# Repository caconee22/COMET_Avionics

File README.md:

# COMET_Avionics

COMET rocket avionics hardware project archive.

This repository replaces the previous `COMET_ROK_2` repository with the full
COMET avionics workspace layout.

## Structure

- `ROK2025/`: ROK2-era module board and reference files.
- `ROK2026/`: Current ROK2026 KiCad projects, shared libraries, and revisions.
- `ROK2026/ROK_3/`: ROK3 small-form-factor and SMD-chip test board.
- `ROK2026/ROK_4/`: ROK4 power-design research test board.
- `ROK2026/Away_1/`: Current active avionics candidate version under development.

## Project History

- `ROK2025/COMET_ROK_2`: First ROK2 circuit and module board. It was not used
  because of software development staffing issues.
- `ROK2026/ROK_3`: Miniaturized ROK3 version with SMD chips. It was not used
  because of power-section issues, but it may still be recoverable and remains
  a test version.
- `ROK2026/ROK_4`: A further test version focused on power-section design. It
  is a research version for a small buck-converter power design.
- `ROK2026/Away_1`: The avionics version candidate intended for actual use. It
  is currently under development.

## Avionics Design Intent

This design intent applies to the whole COMET avionics board family.

## 설계 목적

COMET_Avionics의 목적은 단순한 데이터 로거가 아니라, 로켓 비행 중 필요한
항공전자 기능을 안정적으로 수행하는 것이다.

가장 중요한 기능은 최고점 판단, 지연 사출 판단, 그리고 실제 사출 작동이다.
로그 저장, 통신, GPS 전송, LED, 부저, 콘솔 출력은 모두 보조 기능이며,
이 기능들이 사출 판단과 작동을 막아서는 안 된다.

## 우선순위 규약

1. 사출 판단과 사출 작동을 최우선으로 둔다.
2. SD카드 기록, LoRa, MQTT, Wi-Fi/LTE, GPS 텔레메트리, LED, 부저, 콘솔은
   사출 경로를 블로킹하지 않아야 한다.
3. 센서 감시는 100Hz 이상을 기본 목표로 한다.
4. 저장과 통신은 큐나 별도 작업으로 분리해 지연이 생겨도 비행 판단에 영향을
   주지 않게 한다.
5. 실제 비행 적용 전에는 회로, 펌웨어, 전원부, 사출부를 별도로 검증해야 한다.

## 센서와 비행 판단

기본 설계 방향은 압력 센서, IMU, 배터리 전압, 사출 감지, GPS 최신값을 함께
다루는 것이다.

`Away_1`의 메인 IMU는 STMicroelectronics `LSM6DSO32XTR`를 채택한다.
이 센서는 3축 가속도, 3축 자이로, 온도 센서를 포함하며, 가속도는 최대
±32g, 자이로는 최대 ±2000dps 범위를 기준으로 사용할 수 있다.

비행 중에는 발사 감지, 최고점 판단, 지연 사출, 착지 판단, 회수 모드 진입을
이벤트로 남긴다. 고도, 필터링된 속도, 가속도 크기, 발사/최고점 판단 점수,
GPS 속도와 방향처럼 후처리가 가능한 값은 가능한 한 뷰어나 분석 도구에서
계산한다.

## 어포지 판단 예비 기준

어포지 판단은 센서 하나만으로 결정하지 않고, 기압 고도, IMU 상태, 시간 조건을
함께 보는 상태머신으로 구성한다. 초기 로켓은 발사 실패, 중간 고도 이후 뒤집힘,
상하 반전, 과격한 회전, 불안정 비행이 생길 수 있으므로 정상 비행만 가정하지
않는다.

기본 상태 흐름은 다음을 기준으로 한다.

1. `PAD`: 발사 전 대기 상태.
2. `LAUNCHED`: 발사 감지 후 상승 시작 상태.
3. `COAST_NORMAL`: 정상 상승/관성 비행으로 판단되는 상태.
4. `UNSTABLE_FLIGHT`: 뒤집힘, 과격한 회전, 고도 상승 이상 등 비정상 비행 상태.
5. `APOGEE_DETECTED`: 어포지 또는 하강 시작이 확인된 상태.
6. `FAILSAFE_DEPLOY`: 센서 이상이나 비정상 비행으로 백업 사출이 필요한 상태.
7. `RECOVERY`: 사출 이후 회수 상태.

정상 어포지 판단은 다음 조건을 함께 본다.

- 발사 감지가 완료되어 있을 것.
- 발사 후 최소 사출 금지 시간이 지났을 것.
- 필터링된 기압 고도 기준 최고 고도를 추적할 것.
- 현재 고도가 최고 고도보다 일정량 이상 낮아질 것.
- 필터링된 수직 속도가 음수 방향일 것.
- 위 조건이 짧은 시간 동안 지속될 것.

초기 기준값은 다음 범위에서 시험하며 조정한다.

- 최소 사출 금지 시간: 발사 후 1~2초.
- 고도 하락 판단: 최고 고도 대비 2~5m 하락.
- 하강 지속 시간: 200~500ms.
- 백업 사출 시간: 예상 어포지 이후를 기준으로 별도 시험값 설정.

비정상 비행 판단은 다음 상황을 감지하는 방향으로 둔다.

- 자이로 회전율이 일정 시간 이상 매우 큰 상태.
- 가속도 방향이 계속 급격하게 바뀌는 상태.
- 발사 후 고도 상승이 거의 없거나 예상보다 빨리 멈추는 상태.
- 고도 상승 후 불규칙한 정체와 하락이 반복되는 상태.
- IMU 축 기준 위아래 판단이 신뢰하기 어려운 상태.

비정상 비행 상태에서는 IMU 적분 고도나 자세 기준 판단에 의존하지 않는다.
기압 고도 변화, 시간 조건, 회전 이상 감지를 우선 사용하고, 필요하면 정상
어포지보다 보수적인 백업 사출 조건으로 전환한다.

개념적인 판단식은 다음과 같다.

```text
if launched and time_since_launch > min_deploy_time:
    if altitude_peak - altitude_filtered > altitude_drop_threshold
       and vertical_velocity_filtered < 0
       and falling_duration > falling_hold_time:
        apogee_detected = true

    if unstable_flight and altitude_not_increasing:
        failsafe_deploy = true

    if time_since_launch > max_flight_time:
        failsafe_deploy = true
```

이 기준은 비행 검증 완료값이 아니라 초기 개발용 예비 기준이다. 실제 임계값은
기체 질량, 모터 추력 곡선, 벤트홀 설계, 지상 시험, 저고도 시험 결과를 보고
조정한다.

## 로그 규약

로그는 텍스트보다 바이너리 형식을 우선한다.

- `LOG`: 고정 길이 센서 샘플
- `EVENT`: 발사, 최고점, 사출, 착지, 전압 변화, SD 오류, 파일 회전, 통신 상태,
  GPS fix/loss, 회수 모드 진입 같은 이벤트 기록

`LOG`에는 시간 코드, 시퀀스 번호, 상태 플래그, 압력, 온도, IMU 가속도/자이로,
최신 GPS 위도/경도/고도, GPS 플래그, 배터리 전압, 사출 센서 상태 같은
raw/minimal 값을 저장하는 방향으로 둔다.

## 로그 동작 흐름

패드 대기 또는 armed 상태에서는 최근 약 3초 분량의 100Hz RAM prebuffer를
유지한다. 평상시 저장은 10Hz 정도로 제한할 수 있다.

발사가 감지되면 발사 직전 prebuffer와 발사 이후 데이터를 100Hz로 저장한다.
최고점/사출 이후 하강 구간은 짧은 시간 단위 파일로 분리하는 방향을 둔다.

착지가 10초 이상 안정적으로 확인되면 고속 로그를 닫고, 회수/저전력 모드로
전환한다. 이 상태에서는 1Hz 수준으로 로그를 줄이고 GPS 위치를 LoRa와 MQTT로
전송하는 것을 목표로 한다.

## 통신과 회수

LoRa 433MHz는 지상국과 회수용 통신을 위한 기본 방향으로 둔다.
MQTT는 온보드 Wi-Fi/LTE 라우터를 통한 원격 모니터링 또는 회수 보조 용도로
사용할 수 있다.

통신 실패는 비행 판단 실패로 이어지면 안 된다. 통신은 가능한 경우 보내고,
안 되는 경우에는 로그와 사출 판단이 계속 살아 있어야 한다.

## 검증 기준

이 문서는 COMET_Avionics 전체 보드에 적용되는 설계 의도와 개발 규약이다.
각 보드는 실제 비행 적용 전 회로, 펌웨어, 전원부, 사출부를 별도로 검증해야
하며, README에 적힌 내용만으로 비행 검증 완료를 의미하지 않는다.

Temporary extraction/work folders such as `tmp/` and `tmp_pdf_kmg/` are not
tracked.

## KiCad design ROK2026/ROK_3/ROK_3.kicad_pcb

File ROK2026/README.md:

# ROK2026

COMET ROK 2026 hardware project workspace.

## Projects

- `ROK_3`: Miniaturized ROK3 SMD-chip test board.
- `ROK_4`: ROK4 power-section design and small buck-converter research board.
- `Away_1`: Active avionics candidate version under development.

## Board Status

- `ROK_3`: Small-form-factor version using SMD chips. It was not used because
  of power-section issues, but it may still be recoverable and remains a test
  version.
- `ROK_4`: Further test version for power-section design. It is a research
  board for the small buck-converter power design.
- `Away_1`: The candidate avionics version intended for actual use. This is the
  current development target.

## Away_1

`Away_1` is the active candidate for the real avionics version.
It is currently under development.

The avionics design intent and development rules apply to the whole board
family and are documented in the root `README.md`.

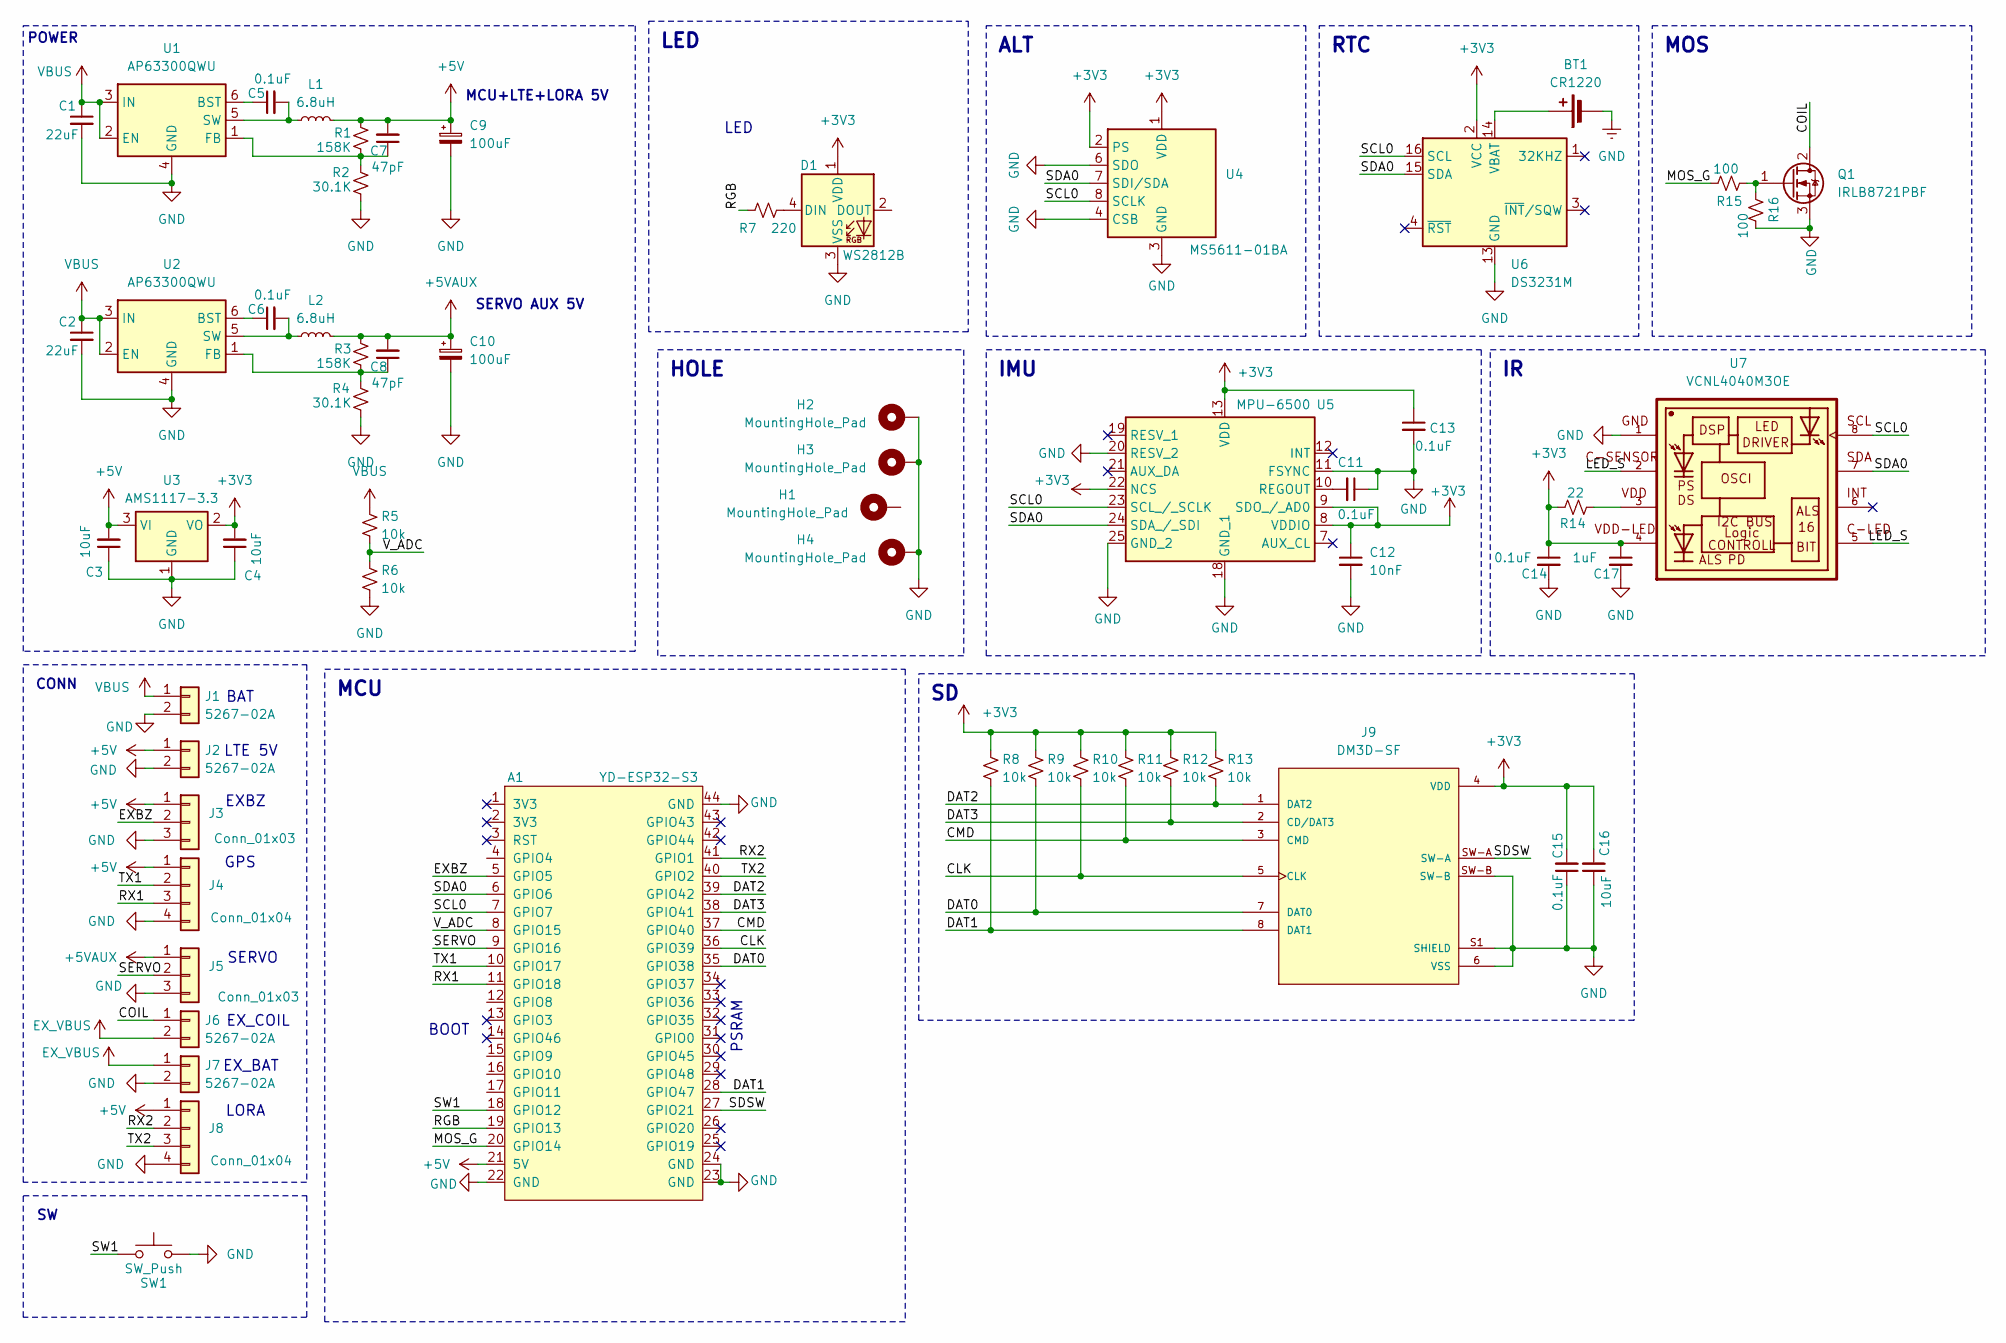
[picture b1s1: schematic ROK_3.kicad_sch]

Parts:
A1: YD-ESP32-S3
BT1: CR1220; S8411-45R_1; Manufacturer_Part_Number CR1220-2; LCSC C70381
C1, C2: 22uF; C_0805_2012Metric
C3, C4, C16: 10uF; C_0805_2012Metric
C5, C6, C14: 0.1uF; C_0805_2012Metric
C7, C8: 47pF; C_0805_2012Metric
C9, C10: 100uF; CP_Elec_6.3x5.3
C11, C13: 0.1uF; C_0805_2012Metric; LCSC C14663
C12: 10nF; C_0805_2012Metric; LCSC C57112
C15: 0.1uF; C_0805_2012Metric; Manufacturer_Part_Number CC0603KRX7R9BB104; LCSC C14663
C17: 1uF; C_0805_2012Metric
D1: WS2812B; LED_WS2812B_PLCC4_5.0x5.0mm_P3.2mm
H1, H2, H3, H4: MountingHole_Pad; MountingHole_3.2mm_M3_DIN965_Pad
J1, J7: 5267-02A; AMASS_XT30U-F_1x02_P5.0mm_Vertical
J2: 5267-02A; Molex_SPOX_5267-02A_1x02_P2.50mm_Vertical
J3, J5: Conn_01x03; Molex_SPOX_5267-03A_1x03_P2.50mm_Vertical
J4, J8: Conn_01x04; Molex_SPOX_5267-04A_1x04_P2.50mm_Vertical
J6: 5267-02A; TerminalBlock_4Ucon_1x02_P3.50mm_Horizontal
J9: DM3D-SF; HRS_DM3D-SF; PARTREV 2017.1
L1, L2: 6.8uH; L_Sumida_CDMC6D28_7.25x6.5mm
Q1: IRLB8721PBF; TO-220-3_Horizontal_TabDown
R1, R3: 158K; R_0805_2012Metric
R2, R4: 30.1K; R_0805_2012Metric
R5, R6, R8, R9, R10, R11, R12, R13: 10k; R_0805_2012Metric; LCSC C25804
R7: 220; R_0805_2012Metric_Pad1.20x1.40mm_HandSolder
R14: 22; R_0805_2012Metric; LCSC C25804
R15, R16: 100; R_0805_2012Metric; LCSC C25804
SW1: SW_Push; SW_PUSH_6mm_H5mm
U1, U2: AP63300QWU; TSOT-23-6
U3: AMS1117-3.3; SOT-223-3_TabPin2
U4: MS5611-01BA; LGA-8_3x5mm_P1.25mm
U5: MPU-6500; QFN-24-1EP_3x3mm_P0.4mm_EP1.75x1.6mm; Manufacturer_Part_Number MPU-6500; Mouser Part Number 410-MPU-6500
U6: DS3231M; SOIC-16W_7.5x10.3mm_P1.27mm
U7: VCNL4040M3OE; VISHAY_VCNL4040_4X2X1.1

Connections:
+3V3: C4.2, C12.1, C13.1, C14.1, C15.2, C16.2, C17.1, D1.1 (VDD), J9.4 (VDD), R8.2, R9.2, R10.2, R11.2, R12.2, R13.2, R14.2, U3.2 (VO), U4.1 (VDD), U4.2 (PS), U5.8 (VDDIO), U5.9 (SDO_/_AD0), U5.13 (VDD), U5.22 (NCS), U6.2 (VCC), U7.4
+5V: A1.21 (5V), C3.2, C7.2, C9.1, J2.1, J3.1, J4.1, J8.1, L1.2, R1.1, U3.3 (VI)
+5VAUX: C8.2, C10.1, J5.1, L2.2, R3.1
/CLK: A1.36 (GPIO39), J9.5 (CLK), R10.1
/CMD: A1.37 (GPIO40), J9.3 (CMD), R11.1
/COIL: J6.1, Q1.2 (D)
/DAT0: A1.35 (GPIO38), J9.7 (DAT0), R9.1
/DAT1: A1.28 (GPIO47), J9.8 (DAT1), R8.1
/DAT2: A1.39 (GPIO42), J9.1 (DAT2), R13.1
/DAT3: A1.38 (GPIO41), J9.2 (CD/DAT3), R12.1
/EXBZ: A1.5 (GPIO5), J3.2
/LED_S: U7.2, U7.5
/MOS_G: A1.20 (GPIO14), R15.2
/RGB: A1.19 (GPIO13), R7.2
/RX1: A1.11 (GPIO18), J4.3
/RX2: A1.41 (GPIO1), J8.2
/SCL0: A1.7 (GPIO7), U4.8 (SCLK), U5.23 (SCL_/_SCLK), U6.16 (SCL), U7.8
/SDA0: A1.6 (GPIO6), U4.7 (SDI/SDA), U5.24 (SDA_/_SDI), U6.15 (SDA), U7.7
/SDSW: A1.27 (GPIO21), J9.SW-A
/SERVO: A1.9 (GPIO16), J5.2
/SW1: A1.18 (GPIO12), SW1.1
/TX1: A1.10 (GPIO17), J4.2
/TX2: A1.40 (GPIO2), J8.3
/V_ADC: A1.8 (GPIO15), R5.1, R6.2
EX_VBUS: J6.2, J7.1
GND: A1.22 (GND), A1.23 (GND), A1.24 (GND), A1.44 (GND), BT1.2 (-), C1.2, C2.2, C3.1, C4.1, C9.2, C10.2, C11.1, C12.2, C13.2, C14.2, C15.1, C16.1, C17.2, D1.3 (VSS), H2.1 (1_1), H3.1 (1_1), H4.1 (1_1), J1.2, J2.2, J3.3, J4.4, J5.3, J7.2, J8.4, J9.6 (VSS), J9.S1 (SHIELD), J9.S2 (SHIELD), J9.S3 (SHIELD), J9.S4 (SHIELD), J9.SW-B, Q1.3 (S), R2.1, R4.1, R6.1, R16.2, SW1.2, U1.4 (GND), U2.4 (GND), U3.1 (GND), U4.3 (GND), U4.4 (CSB), U4.5 (CSB), U4.6 (SDO), U5.11 (FSYNC), U5.18 (GND_1), U5.20 (RESV_2), U5.25 (GND_2), U6.5 (GND), U6.6 (GND), U6.7 (GND), U6.8 (GND), U6.9 (GND), U6.10 (GND), U6.11 (GND), U6.12 (GND), U6.13 (GND), U7.1
unnamed: BT1.1 (+), U6.14 (VBAT)
unnamed: D1.4 (DIN), R7.1
unnamed: Q1.1 (G), R15.1, R16.1
unnamed: R14.1, U7.3
unnamed: C5.1, U1.6 (BST)
unnamed: C7.1, R1.2, R2.2, U1.1 (FB)
unnamed: C5.2, L1.1, U1.5 (SW)
unnamed: C6.1, U2.6 (BST)
unnamed: C8.1, R3.2, R4.2, U2.1 (FB)
unnamed: C6.2, L2.1, U2.5 (SW)
unnamed: C11.2, U5.10 (REGOUT)
VBUS: C1.1, C2.1, J1.1, R5.2, U1.2 (EN), U1.3 (IN), U2.2 (EN), U2.3 (IN)

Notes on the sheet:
EXBZ
EX_BAT
GPS
POWER
EX_COIL
BOOT
BAT
SERVO AUX 5V
PSRAM
MCU+LTE+LORA 5V
LED
LTE 5V
LORA
CONN
SERVO
ALT
MOS
IMU
MCU
RTC
HOLE

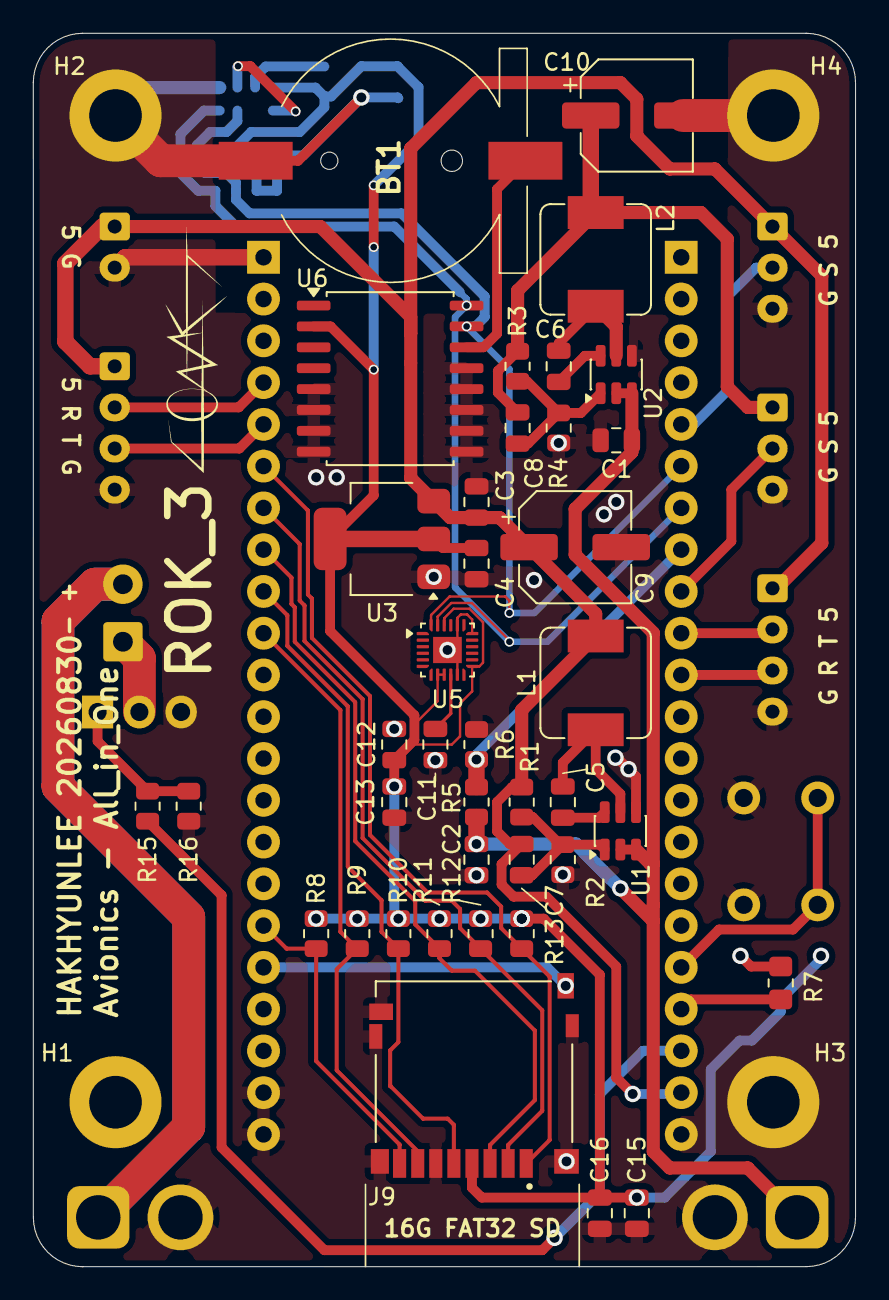
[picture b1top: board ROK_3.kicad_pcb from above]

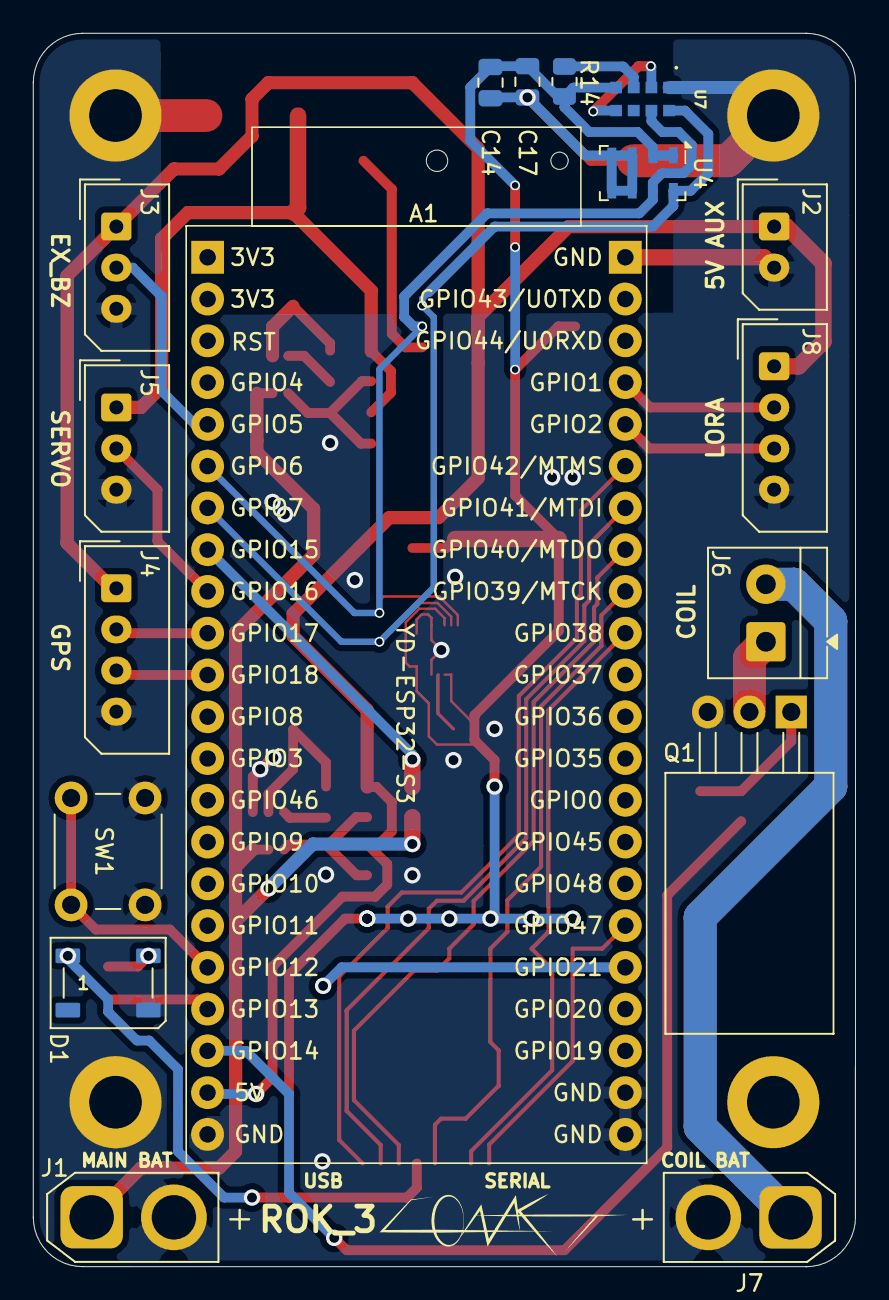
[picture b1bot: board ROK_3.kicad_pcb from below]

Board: 2 copper layers, 50.0 x 75.0 mm, 60 parts (17 on the bottom side), 38 nets.

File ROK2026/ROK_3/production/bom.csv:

Designator,Footprint,Quantity,Value,LCSC Part #
A1,YD-ESP32-S3,1,YD-ESP32-S3,
BT1,S8411-45R_1,1,CR1220,C70381
"C1, C2",0805,2,22uF,
"C10, C9",CP_Elec_6.3x5.3,2,100uF,
"C11, C13, C15",0805,3,0.1uF,C14663
C12,0805,1,10nF,C57112
"C14, C5, C6",0805,3,0.1uF,
"C16, C3, C4",0805,3,10uF,
C17,0805,1,1uF,
"C7, C8",0805,2,47pF,
D1,LED_WS2812B_PLCC4_5.0x5.0mm_P3.2mm,1,WS2812B,
"J1, J7",AMASS_XT30U-F_1x02_P5.0mm_Vertical,2,5267-02A,
J2,Molex_SPOX_5267-02A_1x02_P2.50mm_Vertical,1,5267-02A,
"J3, J5",Molex_SPOX_5267-03A_1x03_P2.50mm_Vertical,2,Conn_01x03,
"J4, J8",Molex_SPOX_5267-04A_1x04_P2.50mm_Vertical,2,Conn_01x04,
J6,TerminalBlock_4Ucon_1x02_P3.50mm_Horizontal,1,5267-02A,
J9,HRS_DM3D-SF,1,DM3D-SF,
"L1, L2",L_Sumida_CDMC6D28_7.25x6.5mm,2,6.8uH,
Q1,TO-220-3_Horizontal_TabDown,1,IRLB8721PBF,
"R1, R3",0805,2,158K,
"R10, R11, R12, R13, R5, R6, R8, R9",0805,8,10k,C25804
R14,0805,1,22,C25804
"R15, R16",0805,2,100,C25804
"R2, R4",0805,2,30.1K,
R7,0805,1,220,
SW1,SW_PUSH_6mm_H5mm,1,SW_Push,
"U1, U2",TSOT-23-6,2,AP63300QWU,
U3,SOT-223-3_TabPin2,1,AMS1117-3.3,
U4,LGA-8_3x5mm_P1.25mm,1,MS5611-01BA,
U5,QFN-24-1EP_3x3mm_P0.4mm_EP1.75x1.6mm,1,MPU-6500,C50278
U6,SOIC-16W_7.5x10.3mm_P1.27mm,1,DS3231M,
U7,VISHAY_VCNL4040_4X2X1.1,1,VCNL4040M3OE,

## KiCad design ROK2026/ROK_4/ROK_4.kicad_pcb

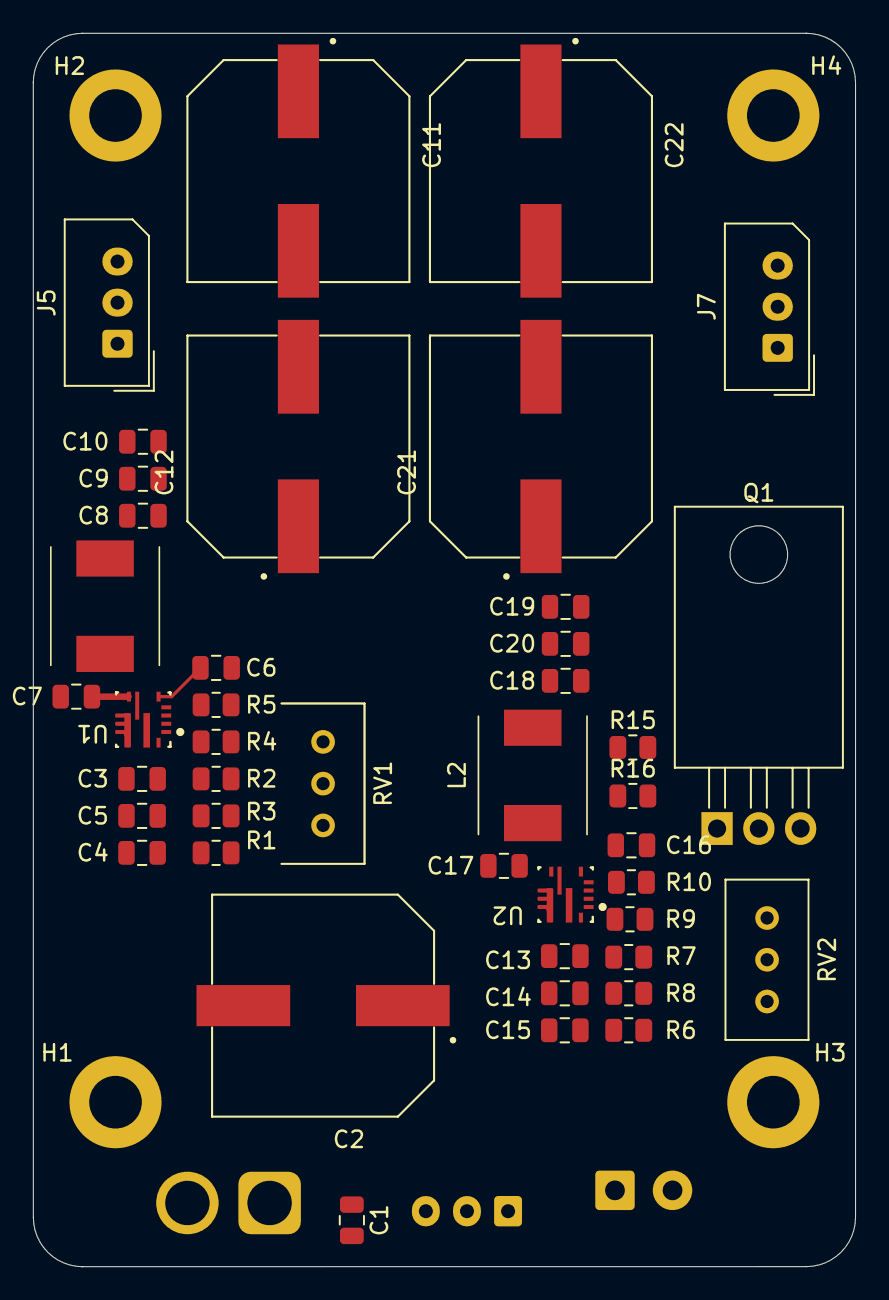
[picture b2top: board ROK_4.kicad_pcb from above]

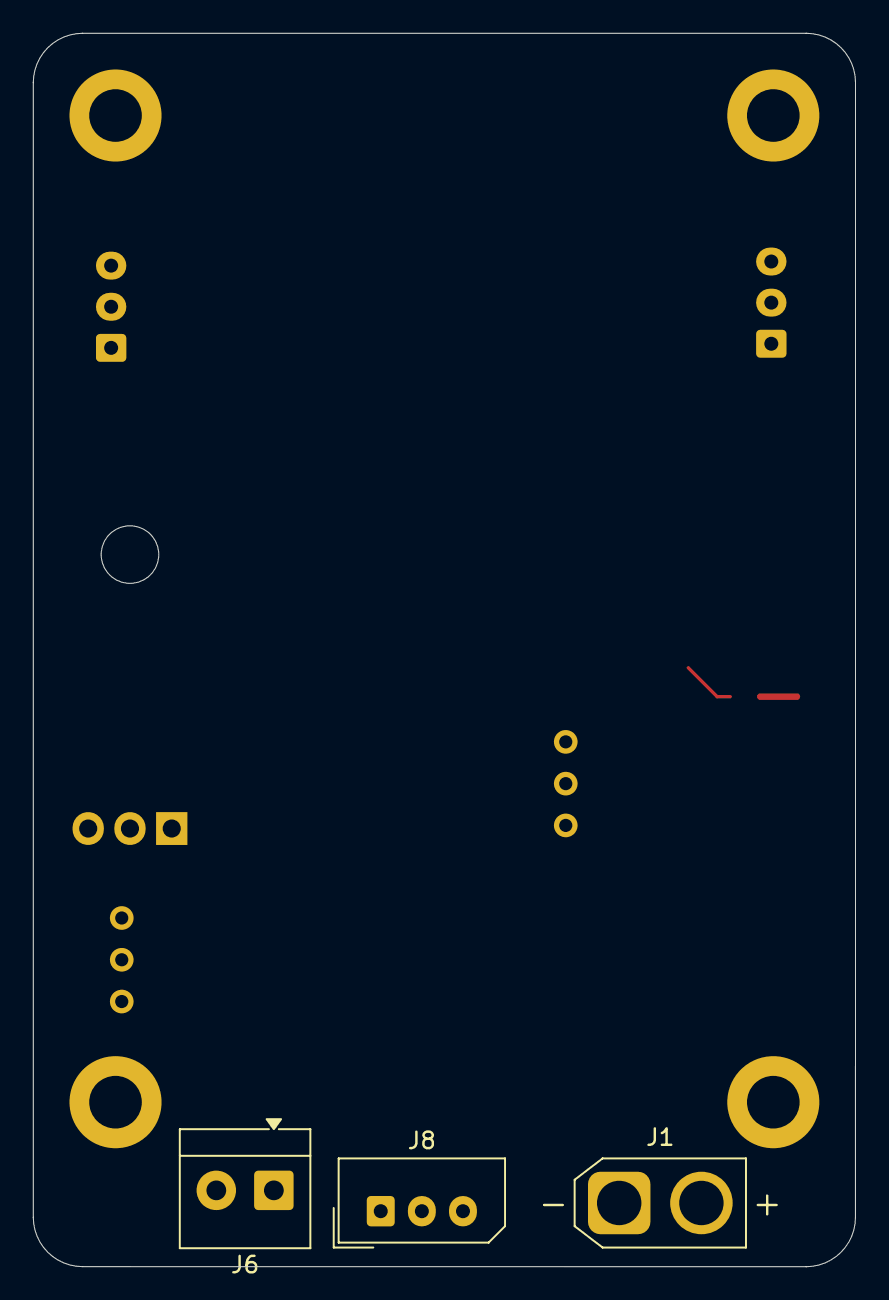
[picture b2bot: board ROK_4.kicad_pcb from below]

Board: 2 copper layers, 50.0 x 75.0 mm, 50 parts (3 on the bottom side), 19 nets.

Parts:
C1, C3, C7, C8, C13, C17, C18: 0.1uF; C_0805_2012Metric
C2, C11, C12, C21, C22: 1000uF; CAP_EEEFK1C182SQ
C4, C5, C9, C10, C14, C15, C19, C20: 10uF; C_0805_2012Metric
C6, C16: 100nF; C_0805_2012Metric
H1, H2, H3, H4: MountingHole_Pad; MountingHole_3.2mm_M3_DIN965_Pad
J1: Conn_01x02; AMASS_XT30U-M_1x02_P5.0mm_Vertical
J5, J7, J8: Conn_01x03; Molex_SPOX_5267-03A_1x03_P2.50mm_Vertical
J6: 5267-02A; TerminalBlock_4Ucon_1x02_P3.50mm_Horizontal
L1, L2: 4.7uH; L_Bourns_SRN6045TA
Q1: IRLB8721PBF; TO-220-3_Horizontal_TabDown
R1, R6: 52.3K; R_0805_2012Metric
R2, R7: 100K; R_0805_2012Metric
R3, R8: 47K; R_0805_2012Metric
R4, R9: 10K; R_0805_2012Metric
R5, R10: 62K; R_0805_2012Metric
R15, R16: 100; R_0805_2012Metric
RV1, RV2: 50K; Potentiometer_Bourns_3296W_Vertical
U1, U2: TPS56A37RPAR; TPS56A37RPAR_RPA0010A_VQFN-HR-10_3x3mm

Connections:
GND: C1.1, C2.2, C3.1, C4.1, C5.1, C6.1, C8.1, C9.1, C10.1, C11.2, C12.2, C13.1, C14.1, C15.1, C16.1, C18.1, C19.1, C20.1, C21.2, C22.2, H2.1 (1_1), H3.1 (1_1), H4.1 (1_1), J1.2, Q1.3 (S), R1.1, R3.2, R4.1, R6.1, R8.2, R9.1, R16.2, U1.3 (AGND), U1.9 (PGND), U2.3 (AGND), U2.9 (PGND)
unnamed: Q1.1 (G), R15.1, R16.1
unnamed: R5.1, RV1.3
unnamed: R10.1, RV2.3
unnamed: C7.2, U1.7 (BOOT)
unnamed: R2.2, R3.1, U1.1 (EN)
unnamed: R4.2, RV1.1, RV1.2, U1.2 (FB)
unnamed: R1.2, U1.10 (MODE)
unnamed: C6.2, U1.5 (SS)
unnamed: C7.1, L1.1, U1.6 (SW)
unnamed: C17.2, U2.7 (BOOT)
unnamed: R7.2, R8.1, U2.1 (EN)
unnamed: R9.2, RV2.1, RV2.2, U2.2 (FB)
unnamed: R6.2, U2.10 (MODE)
unnamed: C16.2, U2.5 (SS)
unnamed: C17.1, L2.1, U2.6 (SW)
SV1: C8.2, C9.2, C10.2, C11.1, C12.1, L1.2, R5.2
SV2: C18.2, C19.2, C20.2, C21.1, C22.1, L2.2, R10.2
VBUS: C1.2, C2.1, C3.2, C4.2, C5.2, C13.2, C14.2, C15.2, J1.1, R2.1, R7.1, U1.8 (VIN), U2.8 (VIN)

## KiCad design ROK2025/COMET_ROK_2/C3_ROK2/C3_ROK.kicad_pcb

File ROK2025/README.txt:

ROKv2.xlsx 에 모든 설명이 있으며 두 시트를 참조하시오
ROK2.zip 파일이 PCB 의 데이터 원본 파일이며 KICAD 로 편집할수있습니다
GB.zip 에 거버파일이 있으며 이를 이요해 같은 PCB 를 생산할수있습니다
C3_ROK2.zip 의 테스트를 위해 구동하던 약간의 예제 코드가 있으며 이는 구동을 위한것이아닌 개발환경 예시를 위함입니다 코딩은 직접 해야합니다
C3_ROK.step 은 모델 파일이며 설개참조를 위해 있습니다

2026/01/20 스마트융합공학과 융합로봇전공 이학현
lhh060508@gmail.com / 010-5034-6220
작성자는 나라를 지키러 갑니다

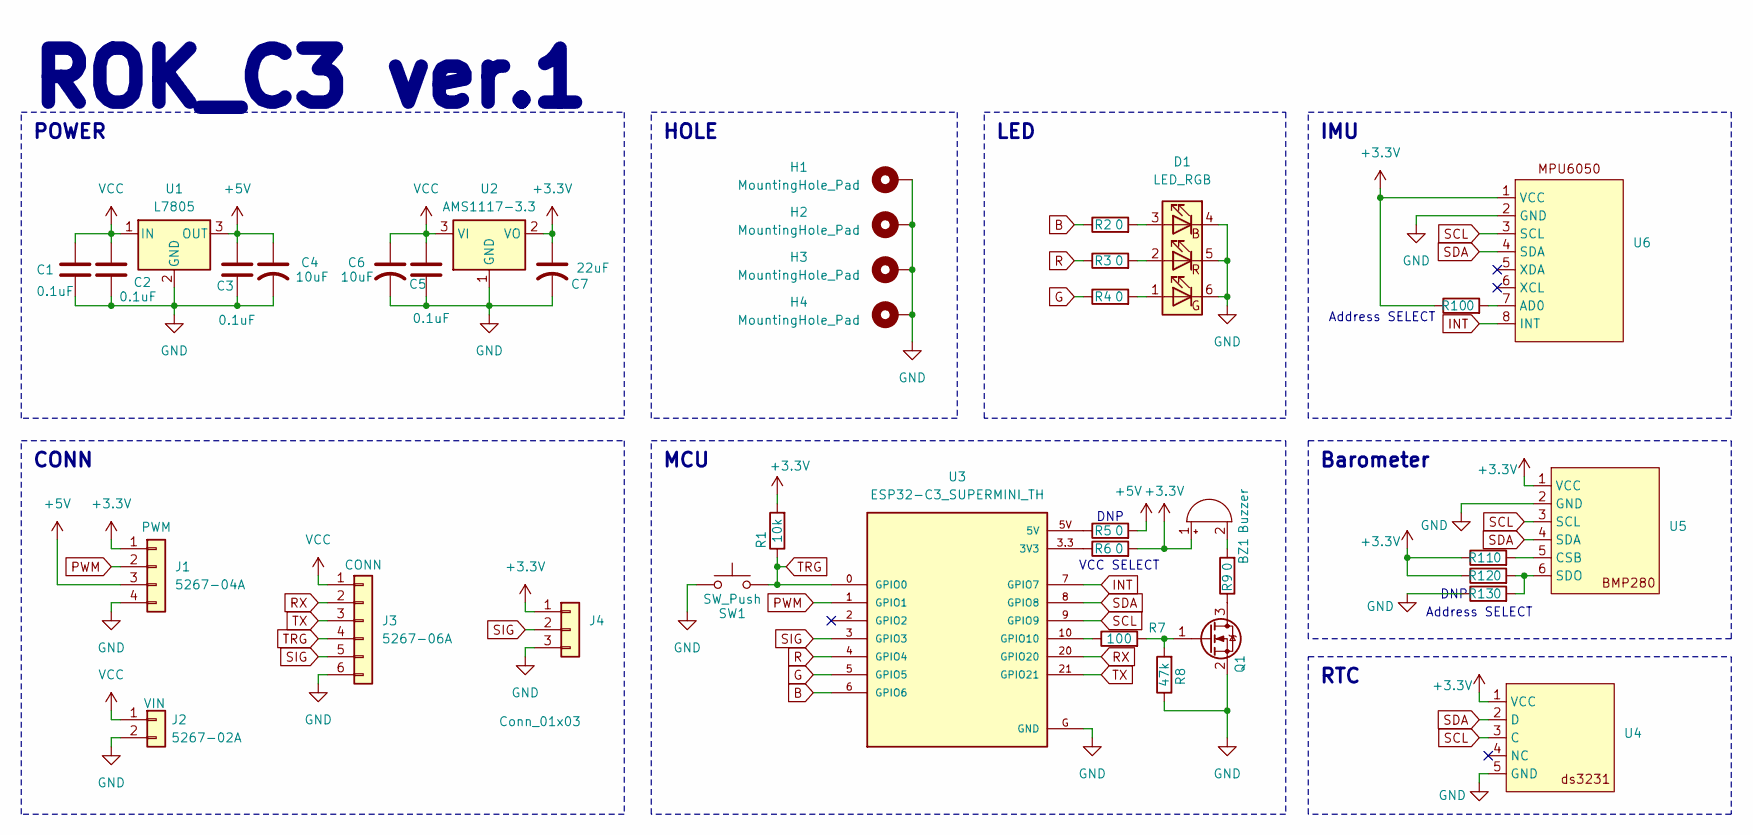
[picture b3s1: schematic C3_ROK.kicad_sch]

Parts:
BZ1: Buzzer; Buzzer_12x9.5RM7.6
C1, C2, C3, C6: 0.1uF; C_0805_2012Metric_Pad1.18x1.45mm_HandSolder
C4: 10uF; CP_Radial_D6.3mm_P2.50mm
C5: 10uF; CP_Radial_D5.0mm_P2.00mm
C7: 22uF; CP_Radial_D5.0mm_P2.00mm
D1: LED_RGB; LED_RGB_5050-6
H1, H2, H3, H4: MountingHole_Pad; MountingHole_3.2mm_M3_DIN965_Pad
J1: 5267-04A; Molex_SPOX_5267-04A_1x04_P2.50mm_Vertical
J2: 5267-02A; Molex_SPOX_5267-02A_1x02_P2.50mm_Vertical
J3: 5267-06A; Molex_SPOX_5267-06A_1x06_P2.50mm_Vertical
J4: Conn_01x03; Molex_SPOX_5267-03A_1x03_P2.50mm_Vertical
Q1: IRLML2402TR; SOT-23_Handsoldering
R1: 10k; R_0805_2012Metric_Pad1.20x1.40mm_HandSolder
R2, R3, R4, R5, R6, R9, R10, R11, R12, R13: 0; R_0805_2012Metric_Pad1.20x1.40mm_HandSolder
R7: 100; R_0805_2012Metric_Pad1.20x1.40mm_HandSolder
R8: 47k; R_0805_2012Metric_Pad1.20x1.40mm_HandSolder
SW1: SW_Push; SW_PUSH_6mm_H5mm
U1: L7805; TO-220-3_Horizontal_TabDown
U2: AMS1117-3.3; SOT-223-3_TabPin2
U3: ESP32-C3_SUPERMINI_TH; MODULE_ESP32-C3_SUPERMINI_TH
U4: ds3231
U5: BMP280
U6: MPU6050

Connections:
+3.3V: BZ1.1 (+), C7.1, J1.1, J4.1, R1.2, R6.2, R10.1, R11.1, R12.1, U2.2 (VO), U4.1 (VCC), U5.1 (VCC), U6.1 (VCC)
+5V: C3.1, C4.1, J1.3, R5.2, U1.3 (OUT)
B: R2.1, U3.6 (GPIO6)
G: R4.1, U3.5 (GPIO5)
GND: C1.2, C2.2, C3.2, C4.2, C5.2, C6.2, C7.2, D1.4 (RK), D1.5 (GK), D1.6 (BK), H1.1, H2.1, H3.1, H4.1, J1.4, J2.2, J3.6 (Can2_shield), J4.3, Q1.2 (S), R8.1, R13.1, SW1.1, U1.2 (GND), U2.1 (GND), U3.G (GND), U4.5 (GND), U5.2 (GND), U6.2 (GND)
INT: U3.7 (GPIO7), U6.8 (INT)
unnamed: BZ1.2 (-), R9.2
unnamed: D1.1 (BA), R4.2
unnamed: D1.2 (GA), R3.2
unnamed: D1.3 (RA), R2.2
unnamed: Q1.3 (D), R9.1
unnamed: Q1.1 (G), R7.2, R8.2
unnamed: R5.1, U3.5V
unnamed: R6.1, U3.3.3 (3V3)
unnamed: R7.1, U3.10 (GPIO10)
unnamed: R11.2, U5.5 (CSB)
unnamed: R12.2, R13.2, U5.6 (SDO)
unnamed: R10.2, U6.7 (AD0)
PWM: J1.2, U3.1 (GPIO1)
R: R3.1, U3.4 (GPIO4)
RX: J3.2 (Can1_L), U3.20 (GPIO20)
SCL: U3.9 (GPIO9), U4.3 (C), U5.3 (SCL), U6.3 (SCL)
SDA: U3.8 (GPIO8), U4.2 (D), U5.4 (SDA), U6.4 (SDA)
SIG: J3.5 (Can1_shiled), J4.2, U3.3 (GPIO3)
TRG: J3.4 (Can2_L), R1.1, SW1.2, U3.0 (GPIO0)
TX: J3.3 (Can2_H), U3.21 (GPIO21)
VCC: C1.1, C2.1, C5.1, C6.1, J2.1, J3.1 (Can1_H), U1.1 (IN), U2.3 (VI)

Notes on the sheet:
VCC SELECT
Address SELECT
DNP
ROK_C3 ver.1
Barometer
MCU
POWER
LED
RTC
CONN
HOLE
IMU

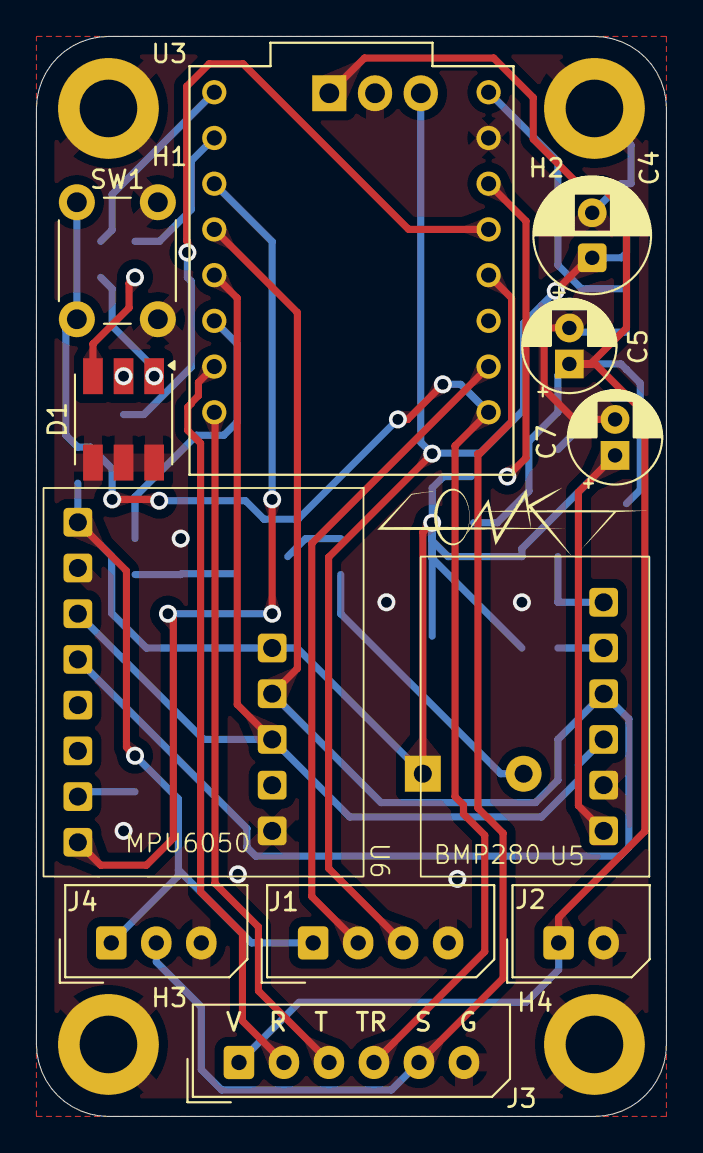
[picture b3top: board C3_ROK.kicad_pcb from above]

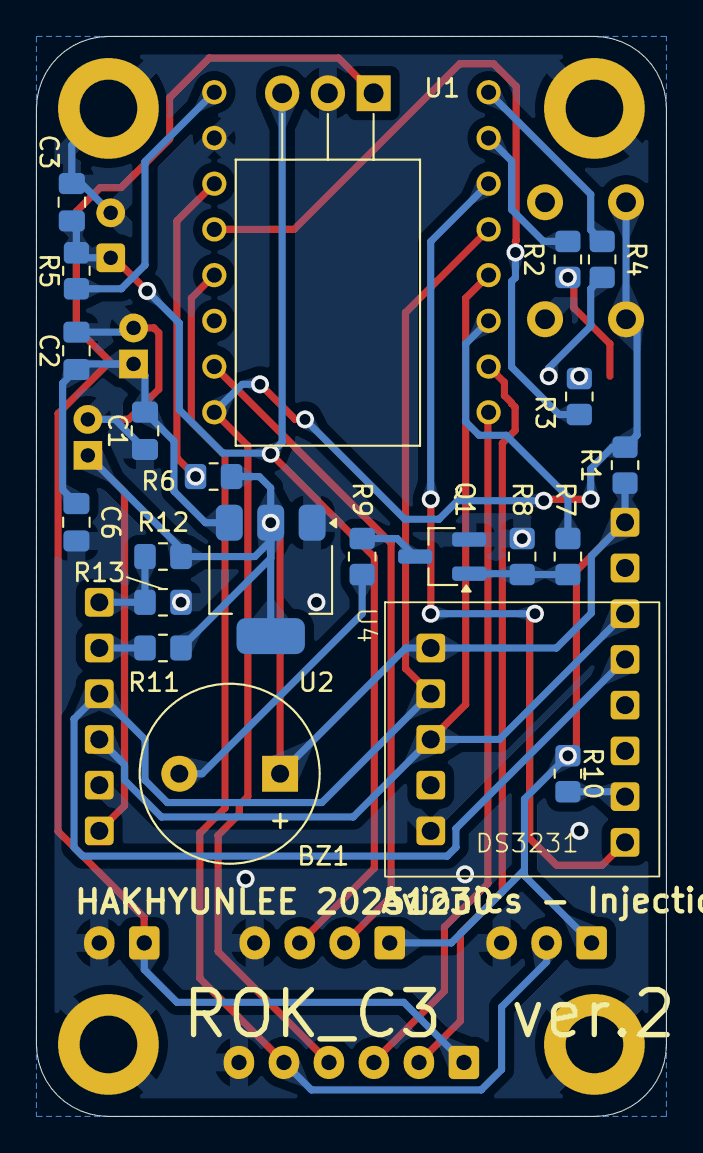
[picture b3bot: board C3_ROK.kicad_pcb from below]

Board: 2 copper layers, 35.0 x 60.0 mm, 38 parts (22 on the bottom side), 27 nets.
